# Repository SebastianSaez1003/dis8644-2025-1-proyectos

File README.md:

# dis8644-2025-1-proyectos

## acerca de

* Sigla: DIS8644
* Nombre: taller de diseño de máquinas eléctricas
* Escuela: Escuela de diseño
* Facultad: Facultad de Arquitectura, Arte y Diseño
* Universidad: Universidad Diego Portales.

dictado durante el primer semestre 2025 (marzo a julio)

## equipo docente

* aarón montoya <https://github.com/montoyamoraga/>
* matías serrano <https://github.com/misaaaaaa>
* andrés martin <https://github.com/AndresMartinM>

## enlaces a carpetas principales

* [00-proyecto-02](./00-proyecto-02/)
  * [00-proyecto-02/grupo-0a](./00-proyecto-02/grupo-0a/)
  * [00-proyecto-02/grupo-0b](./00-proyecto-02/grupo-0b/)
  * [00-proyecto-02/grupo-0c](./00-proyecto-02/grupo-0c/)
  * [00-proyecto-02/grupo-01](./00-proyecto-02/grupo-01/)
  * [00-proyecto-02/grupo-02](./00-proyecto-02/grupo-02/)
  * [00-proyecto-02/grupo-03](./00-proyecto-02/grupo-03/)
  * [00-proyecto-02/grupo-04](./00-proyecto-02/grupo-04/)
  * [00-proyecto-02/grupo-05](./00-proyecto-02/grupo-05/)
  * [00-proyecto-02/grupo-06](./00-proyecto-02/grupo-06/)
* [00-examen](./00-examen/)
  * [00-examen/grupo-0a](./00-examen/grupo-0a/)
  * [00-examen/grupo-0b](./00-examen/grupo-0b/)
  * [00-examen/grupo-0c](./00-examen/grupo-0c/)
  * [00-examen/grupo-01](./00-examen/grupo-01/)
  * [00-examen/grupo-02](./00-examen/grupo-02/)
  * [00-examen/grupo-03](./00-examen/grupo-03/)
  * [00-examen/grupo-04](./00-examen/grupo-04/)
  * [00-examen/grupo-05](./00-examen/grupo-05/)
  * [00-examen/grupo-06](./00-examen/grupo-06/)

## enlaces a carpetas de docentes

* [00-docentes](./00-docentes/)
* [00-info](./00-info/)

## enlaces a cada carpeta de estudiantes

* [01-sofiacartes](./01-sofiacartes/)
* [02-hazzaily](./02-hazzaily/)
* [03-antocristi](./03-antocristi/)
* [04-bumwox](./04-bumwox/)
* [05-brauliofigueroa2001](./05-brauliofigueroa2001/)
* [06-antfuentealba](./06-antfuentealba/)
* [07-clifford1one](./07-clifford1one/)
* [08-isabellagutierrezm](./08-isabellagutierrezm/)
* [98-Bernardita-lobo](./09-Bernardita-lobo/)
* [10-Anaisbmg](./10-Anaisbmg/)
* [11-zaaaiko](./11-zaaaiko/)
* [12-jotamorales-romulus](./12-jotamorales-romulus/)
* [13-Camila-Parada](./13-Camila-Parada/)
* [14-sofia-perezm](./14-sofia-perezm/)
* [15-sz-mada](./15-sz-mada/)
* [16-katalinariquelme](./16-katalinariquelme/)
* [17-felix-rg416](./17-felix-rg416/)
* [18-vxlentiinaa](./18-vxlentiinaa/)
* [19-SebastianSaez1003](./19-SebastianSaez1003/)
* [20-thyare08](./20-thyare08/)
* [21-duckusu](./21-duckusu/)
* [22-HSB25](./22-HSB25/)
* [23-FranUDP](./23-FranUDP/)
* [24-paulinavargasf](./24-paulinavargasf/)
* [25-AlanisMria](./25-AlanisMria/)
* [26-IzhakVillegas](./26-IzhakVillegas/)

## sesiones

nuestras sesiones de clases serán los martes y viernes entre marzo y julio 2025.

* 08:30am - 09:00am: preparación inicial, resolver dudas
* 09:00am - 10:30am: primera parte, foco contenidos y trabajo grupal de taller
* 10:30am - 11:00am: pausa
* 11:00am - 12:30pm: segunda parte, foco retroalimentación a estudiantes

## calendario detallado

| sesión                        | fecha    | temas                            |
| :---------------------------- | :--------| :--------------------------------|
| [13a](00-docentes/sesion-13a/)| 06-03 mar| feedback sobre proyecto-02       |
| [13b](00-docentes/sesion-13b/)| 06-06 vie| visita mbate - grupos proyecto-02|
| [14a](00-docentes/sesion-14a/)| 06-10 mar| prototipado proyecto-02: input   |
| [14b](00-docentes/sesion-14b/)| 06-13 vie| prototipado proyecto-02: output  |
| [15a](00-docentes/sesion-15a/)| 06-17 mar| prototipado proyecto-02          |
| [15b](00-docentes/sesion-15b/)| 06-20 vie| feriado, entrega noche anterior  |
| [16a](00-docentes/sesion-16a/)| 06-24 mar| salida:  palacio pereira         |
| [16b](00-docentes/sesion-16b/)| 06-27 vie| preparación examen - carcasas    |
| [00-examen](00-examen/)       | 07-11 vie| preparación examen - carcasas    |

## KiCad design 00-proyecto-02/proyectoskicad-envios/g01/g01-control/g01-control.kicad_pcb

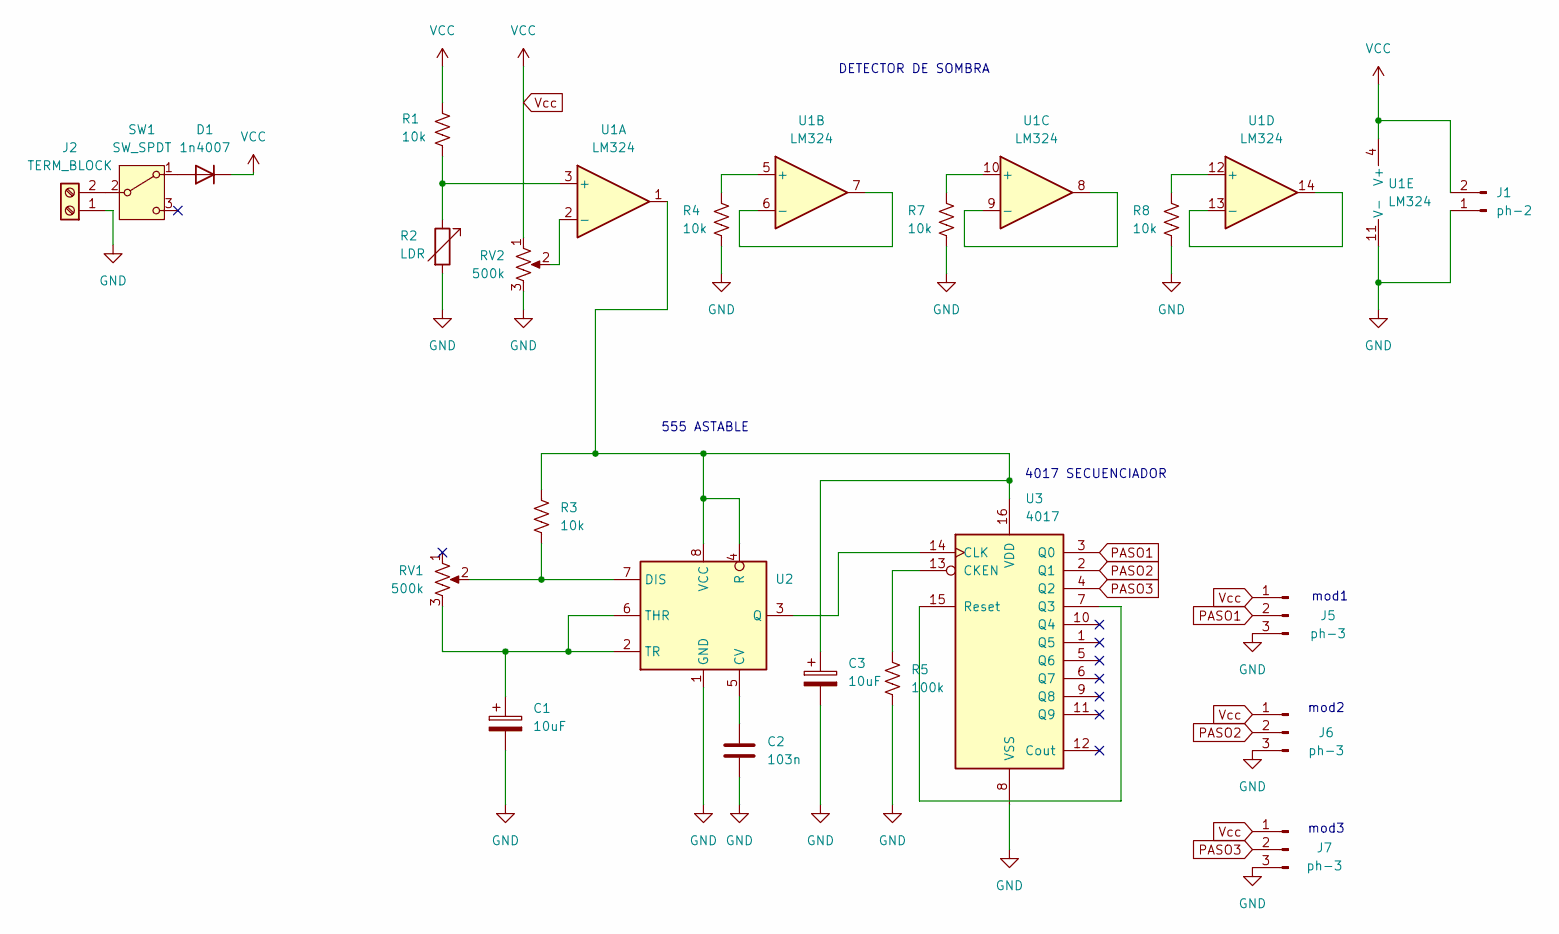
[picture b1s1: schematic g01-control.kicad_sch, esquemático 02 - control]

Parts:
C1, C3: 10uF; CP_Radial_D6.3mm_P2.50mm
C2: 103n; C_Disc_D6.0mm_W2.5mm_P5.00mm
D1: 1n4007; D_DO-41_SOD81_P10.16mm_Horizontal
J1: ph-2; PinHeader_1x02_P2.54mm_Vertical
J2: TERM_BLOCK; TerminalBlock_bornier-2_P5.08mm
J5, J6, J7: ph-3; PinHeader_1x03_P2.54mm_Vertical
R1, R3, R4, R7, R8: 10k; R_Axial_DIN0207_L6.3mm_D2.5mm_P10.16mm_Horizontal
R2: LDR; R_LDR_4.9x4.2mm_P2.54mm_Vertical
R5: 100k; R_Axial_DIN0207_L6.3mm_D2.5mm_P10.16mm_Horizontal
RV1, RV2: 500k; Potentiometer_Alps_RK163_Single_Horizontal
SW1: SW_SPDT; SW_Slide-03_Wuerth-WS-SLTV_10x2.5x6.4_P2.54mm
U1: LM324; DIP-14_W7.62mm_Socket_LongPads
U2: DIP-8_W7.62mm_Socket_LongPads
U3: 4017; DIP-16_W7.62mm_Socket_LongPads

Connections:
GND: C1.2, C2.2, C3.2, J1.1, J2.1, J5.3, J6.3, J7.3, R2.2, R4.2, R5.2, R7.2, R8.2, RV2.3, U1.11 (V-), U2.1 (GND), U3.8 (VSS); also elsewhere on the board
unnamed: D1.2 (A), SW1.1 (A)
unnamed: J2.2, SW1.2 (B)
unnamed: R1.2, R2.1, U1.3 (+)
unnamed: RV2.2, U1.2 (-)
unnamed: R4.1, U1.5 (+)
unnamed: U1.6 (-), U1.7
unnamed: R7.1, U1.10 (+)
unnamed: U1.8, U1.9 (-)
unnamed: R8.1, U1.12 (+)
unnamed: U1.13 (-), U1.14
unnamed: C2.1, U2.5 (CV)
unnamed: R3.2, RV1.2, U2.7 (DIS)
unnamed: U2.3 (Q), U3.14 (CLK)
unnamed: C3.1, R3.1, U1.1, U2.4 (R), U2.8 (VCC), U3.16 (VDD)
unnamed: C1.1, RV1.3, U2.2 (TR), U2.6 (THR)
unnamed: R5.1, U3.13 (CKEN)
unnamed: U3.7 (Q3), U3.15 (Reset)
PASO1: J5.2, U3.3 (Q0)
PASO2: J6.2, U3.2 (Q1)
PASO3: J7.2, U3.4 (Q2)
Vcc: D1.1 (K), J1.2, J5.1, J6.1, J7.1, R1.1, RV2.1, U1.4 (V+)

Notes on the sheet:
mod2
4017 SECUENCIADOR
555 ASTABLE
mod3
DETECTOR DE SOMBRA
mod1

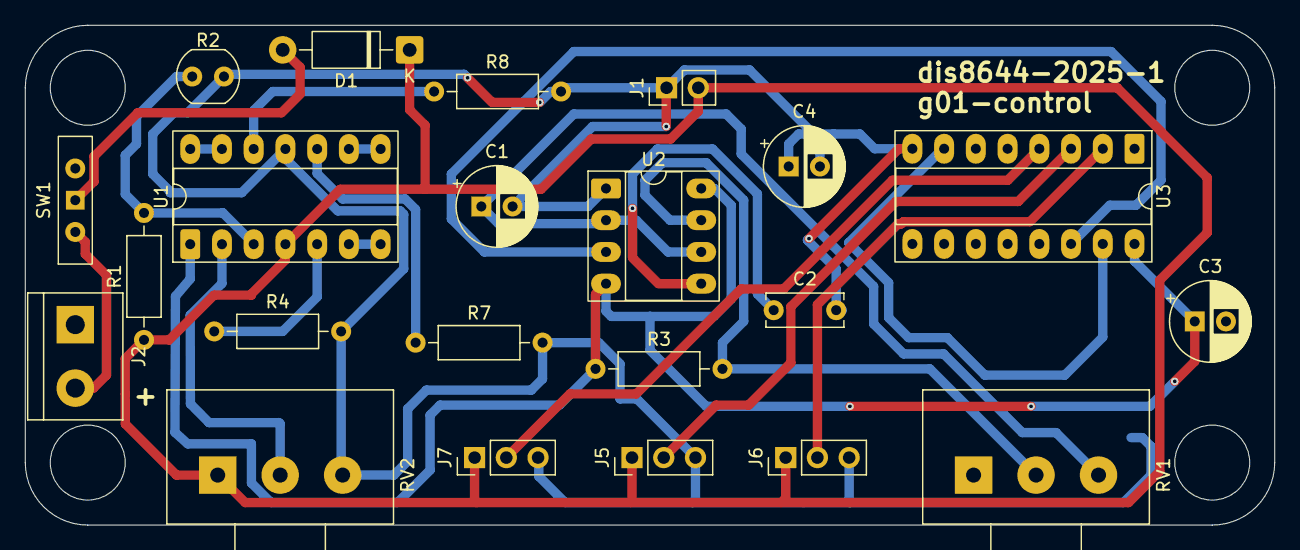
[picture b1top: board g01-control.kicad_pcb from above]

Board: 2 copper layers, 100.0 x 40.0 mm, 22 parts (0 on the bottom side), 21 nets.

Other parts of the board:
C4: 10uF; CP_Radial_D6.3mm_P2.50mm

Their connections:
GND: C4.1, C4.2; also elsewhere on the board

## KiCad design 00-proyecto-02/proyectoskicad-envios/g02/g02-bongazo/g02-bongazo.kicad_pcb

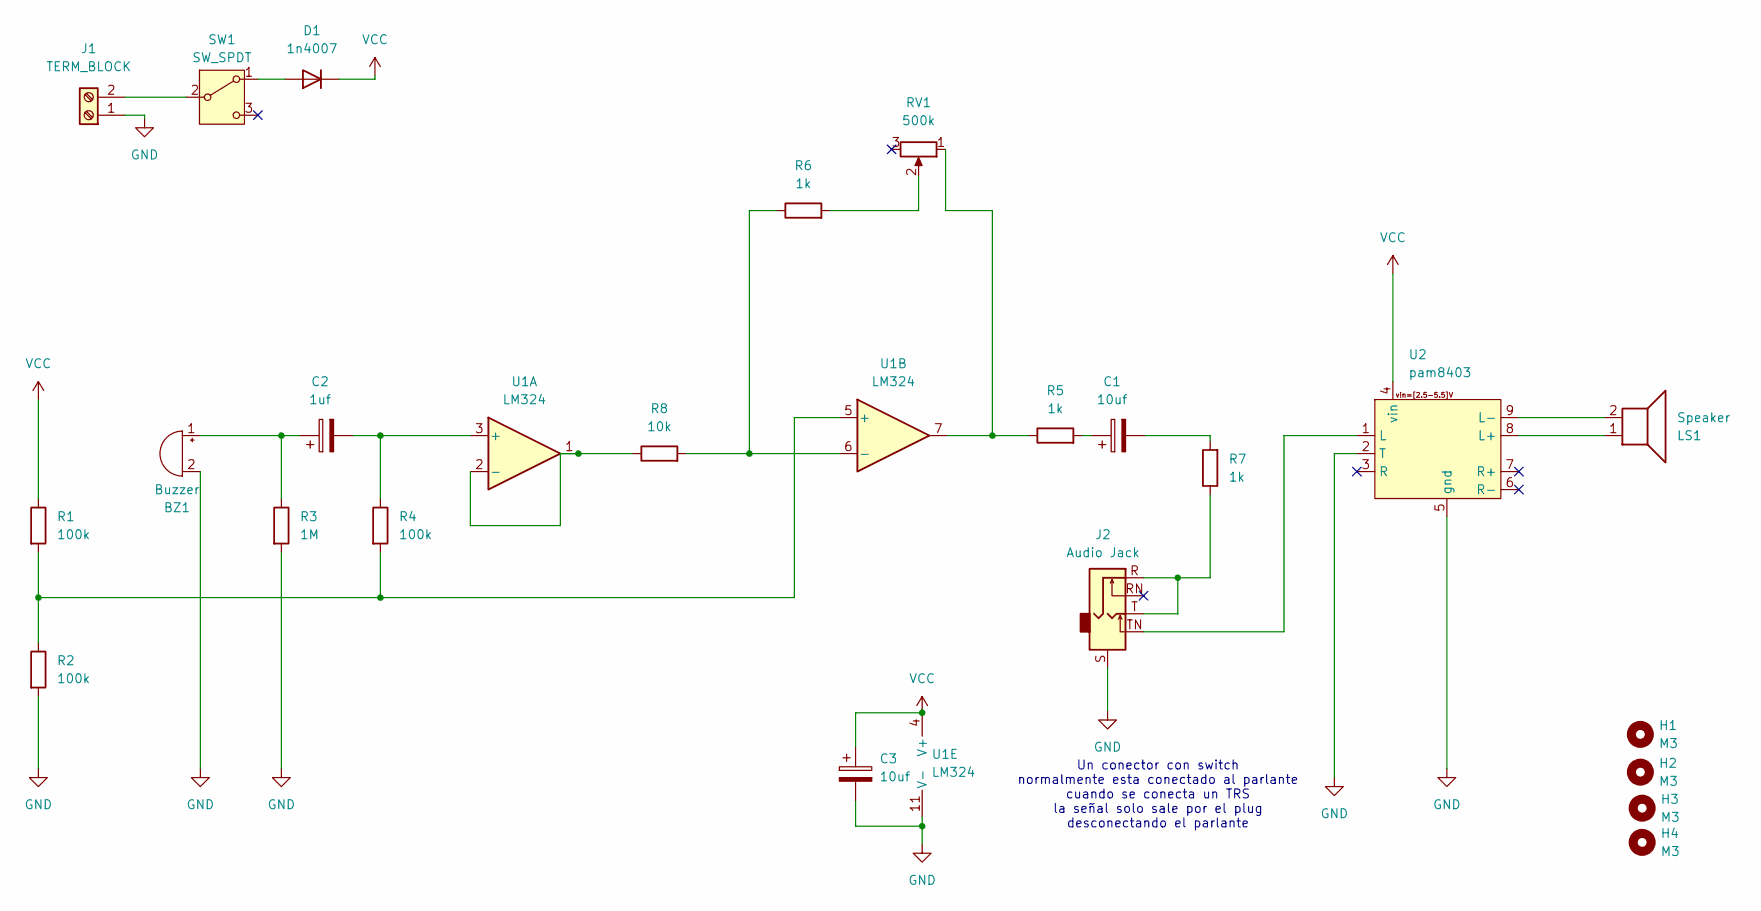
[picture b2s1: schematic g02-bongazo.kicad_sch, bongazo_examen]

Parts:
BZ1: Buzzer; Buzzer_12x9.5RM7.6
C1, C3: 10uf; CP_Radial_D6.3mm_P2.50mm
C2: 1uf; CP_Radial_D6.3mm_P2.50mm
D1: 1n4007; D_DO-41_SOD81_P12.70mm_Horizontal
H1, H2, H3, H4: M3; MountingHole_3.2mm_M3
J1: TERM_BLOCK; TerminalBlock_bornier-2_P5.08mm
J2: Audio Jack; Jack_6.35mm_Neutrik_NRJ6HM-1-AU_Horizontal
LS1: Speaker; TerminalBlock_MaiXu_MX126-5.0-02P_1x02_P5.00mm
R1, R2, R4: 100k; R_Axial_DIN0207_L6.3mm_D2.5mm_P10.16mm_Horizontal
R3: 1M; R_Axial_DIN0207_L6.3mm_D2.5mm_P10.16mm_Horizontal
R5, R6, R7: 1k; R_Axial_DIN0207_L6.3mm_D2.5mm_P10.16mm_Horizontal
R8: 10k; R_Axial_DIN0207_L6.3mm_D2.5mm_P10.16mm_Horizontal
RV1: 500k; Potentiometer_Alps_RK163_Single_Horizontal
SW1: SW_SPDT; SW_Slide-03_Wuerth-WS-SLTV_10x2.5x6.4_P2.54mm
U1: LM324; DIP-14_W7.62mm
U2: pam8403

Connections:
GND: BZ1.2 (-), C3.2, J1.1, J2.S, R2.2, R3.2, U1.11 (V-), U2.2 (T), U2.5 (gnd)
unnamed: BZ1.1 (+), C2.1, R3.1
unnamed: C1.1, R5.2
unnamed: C1.2, R7.2
unnamed: D1.2 (A), SW1.1 (A)
unnamed: J1.2, SW1.2 (B)
unnamed: J2.R, J2.T, R7.1
unnamed: R5.1, RV1.1, U1.7
unnamed: R6.2, RV1.2
unnamed: C2.2, R4.1, U1.3 (+)
unnamed: R8.1, U1.1, U1.2 (-)
unnamed: R1.2, R2.1, R4.2, U1.5 (+)
unnamed: R6.1, R8.2, U1.6 (-)
unnamed: J2.TN, U2.1 (L)
unnamed: LS1.1, U2.8 (L+)
unnamed: LS1.2, U2.9 (L-)
VCC: C3.1, D1.1 (K), R1.1, U1.4 (V+), U2.4 (vin)

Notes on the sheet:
Un conector con switch normalmente esta conectado al parlante cuando se conecta un TRS la señal solo sale por el plug desconectando el parlante

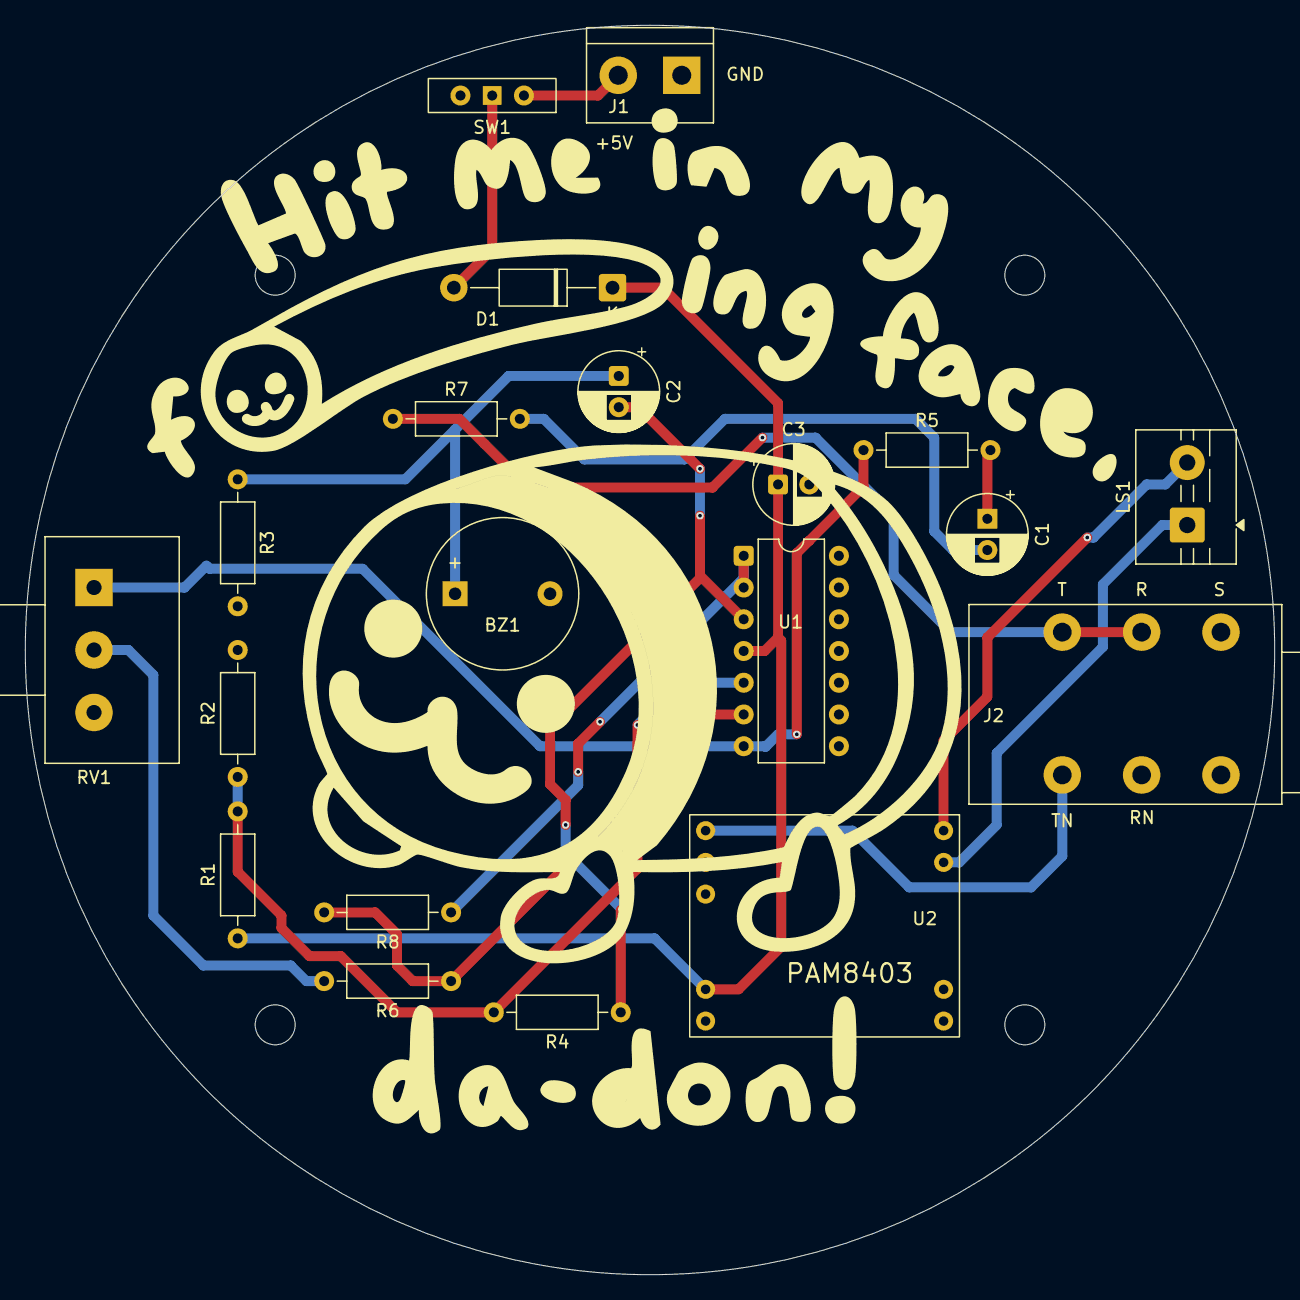
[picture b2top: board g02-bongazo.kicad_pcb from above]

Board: 2 copper layers, 100.0 x 100.0 mm, 24 parts (0 on the bottom side), 17 nets.

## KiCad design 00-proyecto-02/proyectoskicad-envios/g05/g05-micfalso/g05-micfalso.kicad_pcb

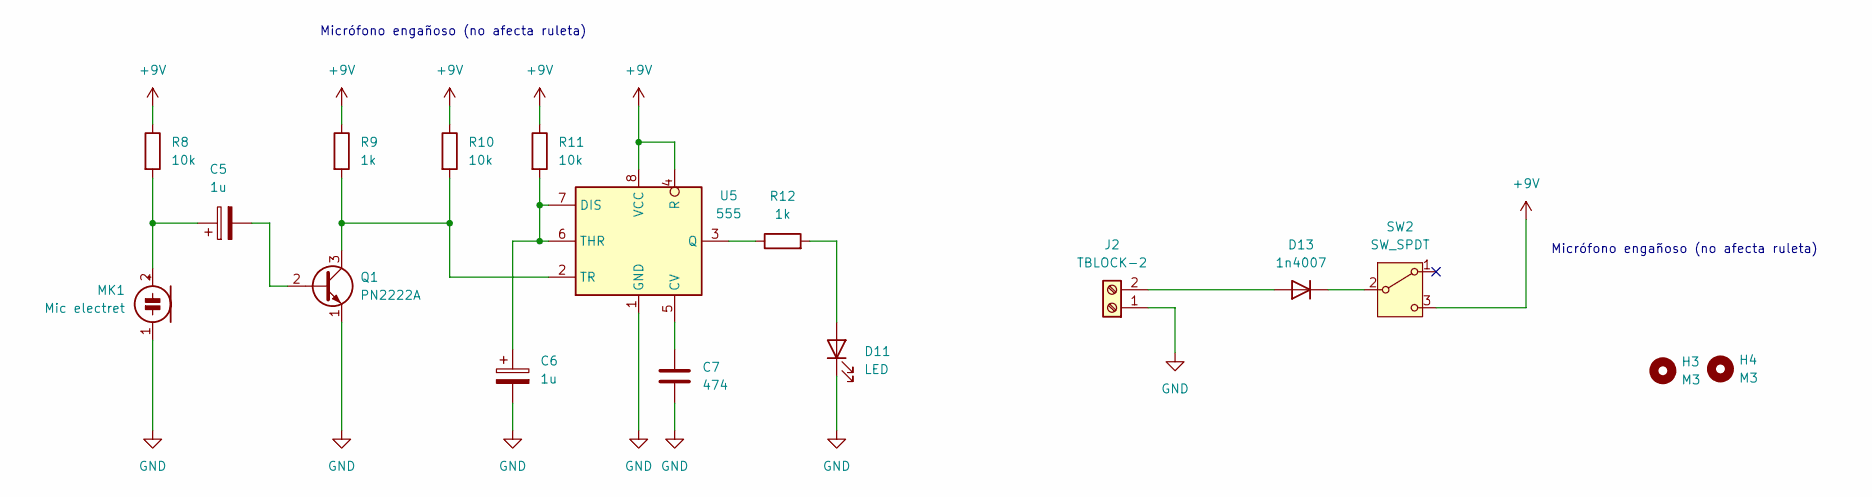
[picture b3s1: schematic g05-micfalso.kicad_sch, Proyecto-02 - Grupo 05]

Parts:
C5, C6: 1u; CP_Radial_D6.3mm_P2.50mm
C7: 474; C_Disc_D5.0mm_W2.5mm_P5.00mm
D11: LED; LED_D5.0mm
D13: 1n4007; D_DO-41_SOD81_P10.16mm_Horizontal
H3, H4: M3; MountingHole_3.2mm_M3
J2: TBLOCK-2; TerminalBlock_MaiXu_MX126-5.0-02P_1x02_P5.00mm
MK1: Mic electret; POM-2244P-C3310-2-R
Q1: PN2222A; TO-92_Inline_Wide
R8, R10, R11: 10k; R_Axial_DIN0207_L6.3mm_D2.5mm_P10.16mm_Horizontal
R9, R12: 1k; R_Axial_DIN0207_L6.3mm_D2.5mm_P10.16mm_Horizontal
SW2: SW_SPDT; SPDT_PCB_small_P2.5mm
U5: 555; DIP-8_W7.62mm_Socket_LongPads

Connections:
+9V: R8.1, R9.1, R10.1, R11.1, SW2.3 (C), U5.4 (R), U5.8 (VCC)
GND: C6.2, C7.2, D11.1 (K), J2.1, MK1.1 (-), Q1.1 (E), U5.1 (GND)
unnamed: D11.2 (A), R12.2
unnamed: D13.2 (A), J2.2
unnamed: D13.1 (K), SW2.2 (B)
unnamed: C5.1, MK1.2 (+), R8.2
unnamed: C5.2, Q1.2 (B)
unnamed: Q1.3 (C), R9.2, R10.2, U5.2 (TR)
unnamed: C7.1, U5.5 (CV)
unnamed: C6.1, R11.2, U5.6 (THR), U5.7 (DIS)
unnamed: R12.1, U5.3 (Q)

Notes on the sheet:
Micrófono engañoso (no afecta ruleta)

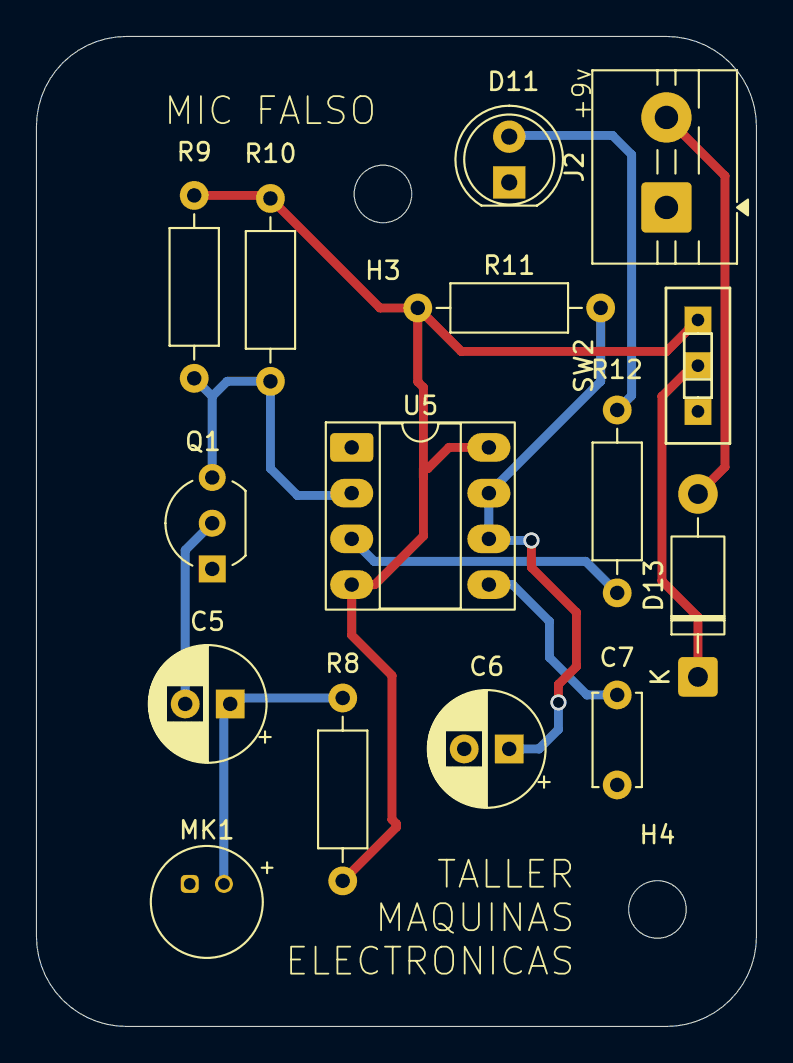
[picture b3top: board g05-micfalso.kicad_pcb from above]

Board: 2 copper layers, 40.0 x 55.0 mm, 17 parts (0 on the bottom side), 11 nets.

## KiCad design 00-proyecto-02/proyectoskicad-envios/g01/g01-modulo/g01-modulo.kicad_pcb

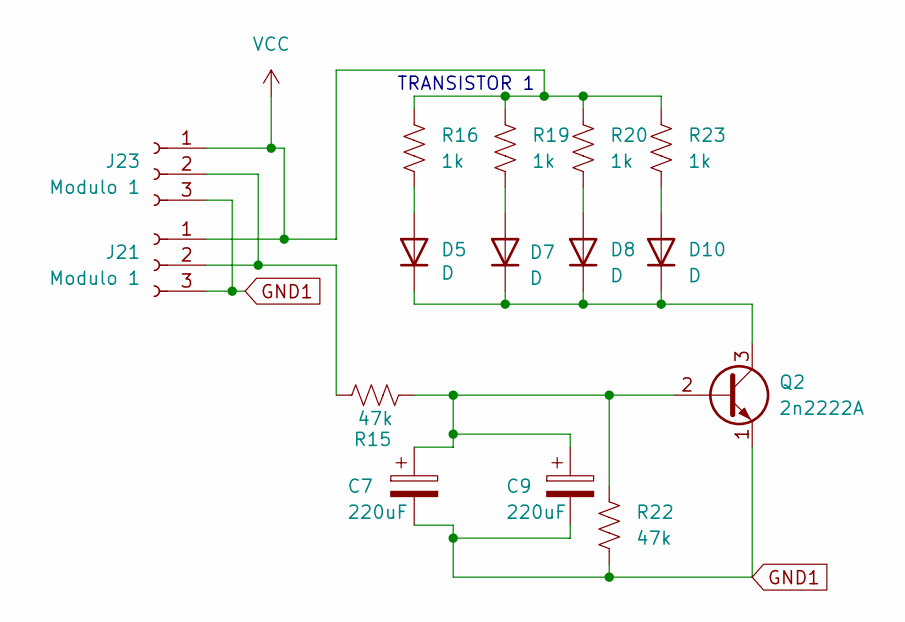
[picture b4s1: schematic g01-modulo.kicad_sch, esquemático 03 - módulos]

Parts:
C7, C9: 220uF; CP_Radial_D6.3mm_P2.50mm
D5, D7, D8, D10: D; LED_D5.0mm
J21, J23: Modulo 1; PinHeader_1x03_P2.54mm_Vertical
Q2: 2n2222A; TO-92
R15, R22: 47k; R_Axial_DIN0207_L6.3mm_D2.5mm_P10.16mm_Horizontal
R16, R19, R20, R23: 1k; R_Axial_DIN0207_L6.3mm_D2.5mm_P10.16mm_Horizontal

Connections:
GND1: C7.2, C9.2, J21.3, J23.3, Q2.1 (E), R22.2
unnamed: D5.2 (A), R16.2
unnamed: D7.2 (A), R19.2
unnamed: D8.2 (A), R20.2
unnamed: D10.2 (A), R23.2
unnamed: D5.1 (K), D7.1 (K), D8.1 (K), D10.1 (K), Q2.3 (C)
unnamed: J21.2, J23.2, R15.1
unnamed: C7.1, C9.1, Q2.2 (B), R15.2, R22.1
VCC: J21.1, J23.1, R16.1, R19.1, R20.1, R23.1

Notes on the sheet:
TRANSISTOR 1

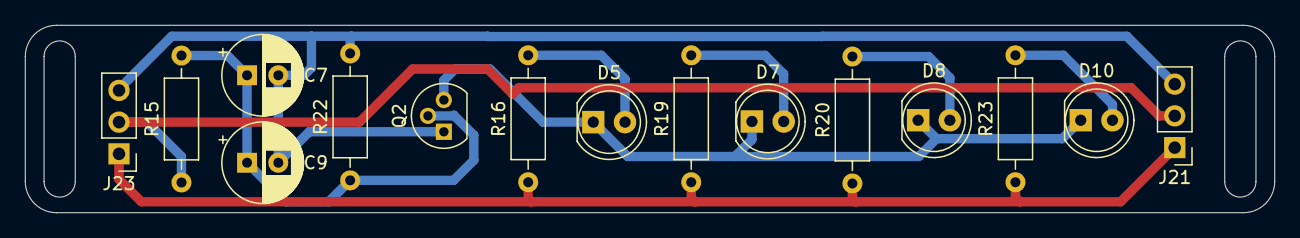
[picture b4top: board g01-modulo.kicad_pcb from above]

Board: 2 copper layers, 100.0 x 15.0 mm, 15 parts (0 on the bottom side), 9 nets.

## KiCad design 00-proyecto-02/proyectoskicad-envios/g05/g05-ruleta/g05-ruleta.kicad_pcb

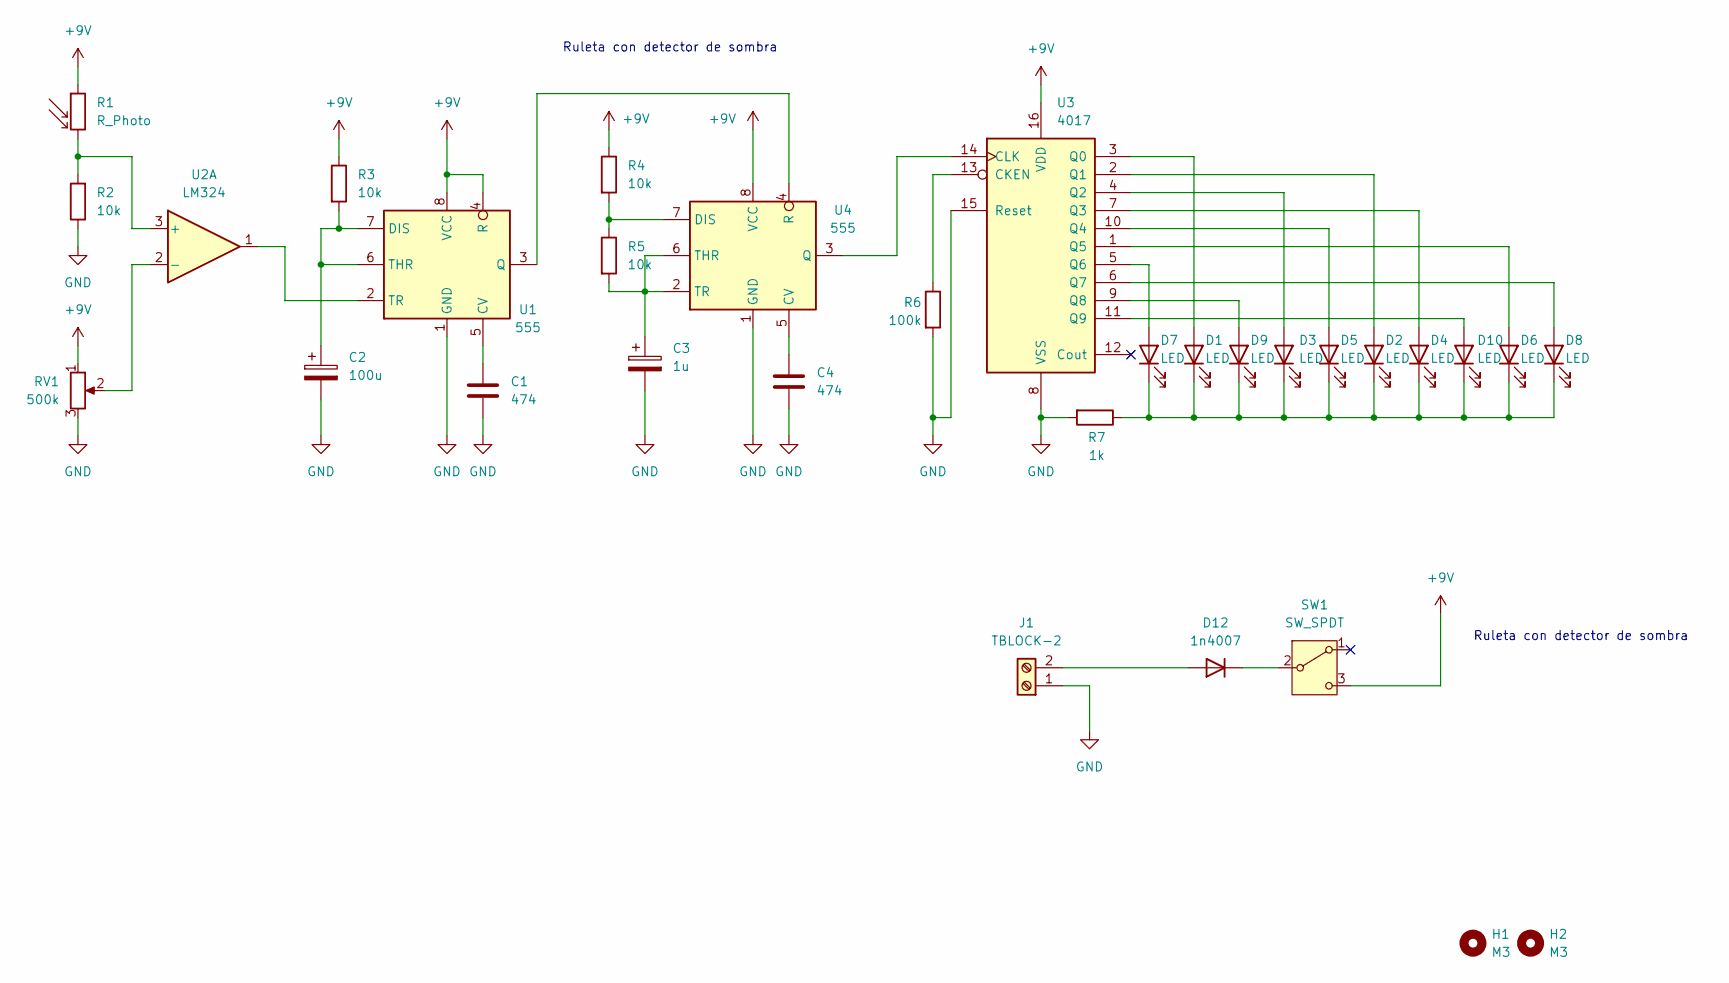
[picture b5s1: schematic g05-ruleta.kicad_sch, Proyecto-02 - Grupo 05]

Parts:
C1, C4: 474; C_Disc_D5.0mm_W2.5mm_P5.00mm
C2: 100u; CP_Radial_D6.3mm_P2.50mm
C3: 1u; CP_Radial_D6.3mm_P2.50mm
D1, D2, D3, D4, D5, D6, D7, D8, D9, D10: LED; LED_D5.0mm
D12: 1n4007; D_DO-41_SOD81_P10.16mm_Horizontal
H1, H2: M3; MountingHole_3.2mm_M3
J1: TBLOCK-2; TerminalBlock_MaiXu_MX126-5.0-02P_1x02_P5.00mm
R1: R_Photo; R_LDR_5.1x4.3mm_P3.4mm_Vertical
R2, R3, R4, R5: 10k; R_Axial_DIN0207_L6.3mm_D2.5mm_P10.16mm_Horizontal
R6: 100k; R_Axial_DIN0207_L6.3mm_D2.5mm_P10.16mm_Horizontal
R7: 1k; R_Axial_DIN0207_L6.3mm_D2.5mm_P10.16mm_Horizontal
RV1: 500k; Potentiometer_Piher_T-16H_Single_Horizontal
SW1: SW_SPDT; SPDT_PCB_small_P2.5mm
U1, U4: 555; DIP-8_W7.62mm_Socket_LongPads
U2: LM324; DIP-14_W7.62mm_Socket_LongPads
U3: 4017; DIP-16_W7.62mm_Socket_LongPads

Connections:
+9V: R1.1, R3.1, R4.1, RV1.1, SW1.3 (C), U1.4 (R), U1.8 (VCC), U3.16 (VDD), U4.8 (VCC)
GND: C1.2, C2.2, C3.2, C4.2, J1.1, R2.1, R6.2, R7.2, RV1.3, U1.1 (GND), U3.8 (VSS), U3.15 (Reset), U4.1 (GND)
unnamed: D1.2 (A), U3.3 (Q0)
unnamed: D1.1 (K), D2.1 (K), D3.1 (K), D4.1 (K), D5.1 (K), D6.1 (K), D7.1 (K), D8.1 (K), D9.1 (K), D10.1 (K), R7.1
unnamed: D2.2 (A), U3.2 (Q1)
unnamed: D3.2 (A), U3.4 (Q2)
unnamed: D4.2 (A), U3.7 (Q3)
unnamed: D5.2 (A), U3.10 (Q4)
unnamed: D6.2 (A), U3.1 (Q5)
unnamed: D7.2 (A), U3.5 (Q6)
unnamed: D8.2 (A), U3.6 (Q7)
unnamed: D9.2 (A), U3.9 (Q8)
unnamed: D10.2 (A), U3.11 (Q9)
unnamed: D12.2 (A), J1.2
unnamed: D12.1 (K), SW1.2 (B)
unnamed: C1.1, U1.5 (CV)
unnamed: C2.1, R3.2, U1.6 (THR), U1.7 (DIS)
unnamed: U1.3 (Q), U4.4 (R)
unnamed: U1.2 (TR), U2.1
unnamed: R1.2, R2.2, U2.3 (+)
unnamed: RV1.2, U2.2 (-)
unnamed: R6.1, U3.13 (CKEN)
unnamed: U3.14 (CLK), U4.3 (Q)
unnamed: C4.1, U4.5 (CV)
unnamed: R4.2, R5.1, U4.7 (DIS)
unnamed: C3.1, R5.2, U4.2 (TR), U4.6 (THR)

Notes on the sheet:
Ruleta con detector de sombra

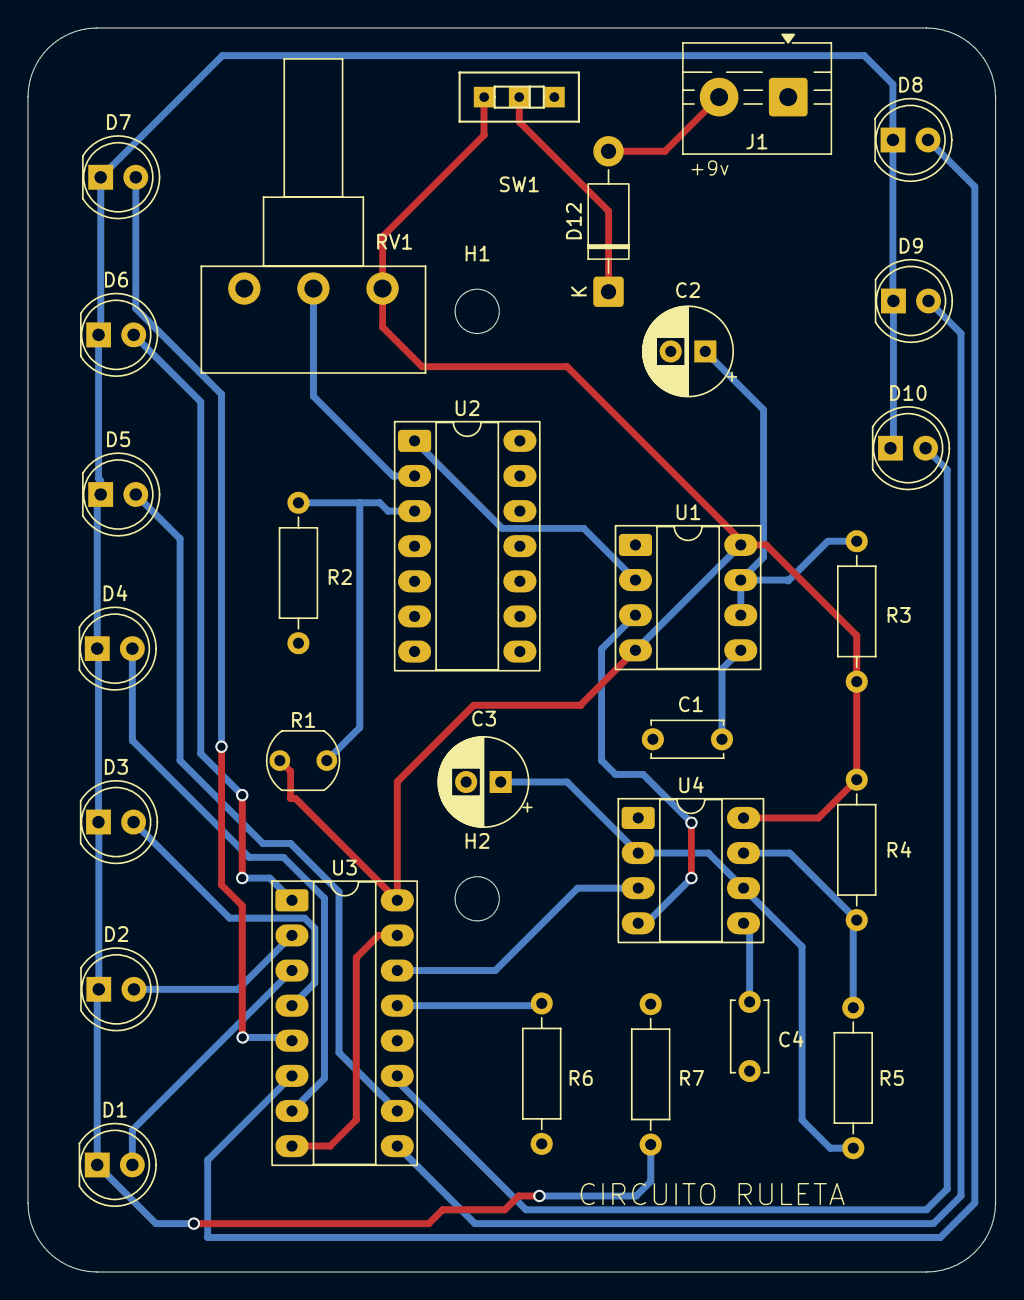
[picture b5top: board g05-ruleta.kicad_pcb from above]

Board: 2 copper layers, 70.0 x 90.0 mm, 31 parts (0 on the bottom side), 26 nets.

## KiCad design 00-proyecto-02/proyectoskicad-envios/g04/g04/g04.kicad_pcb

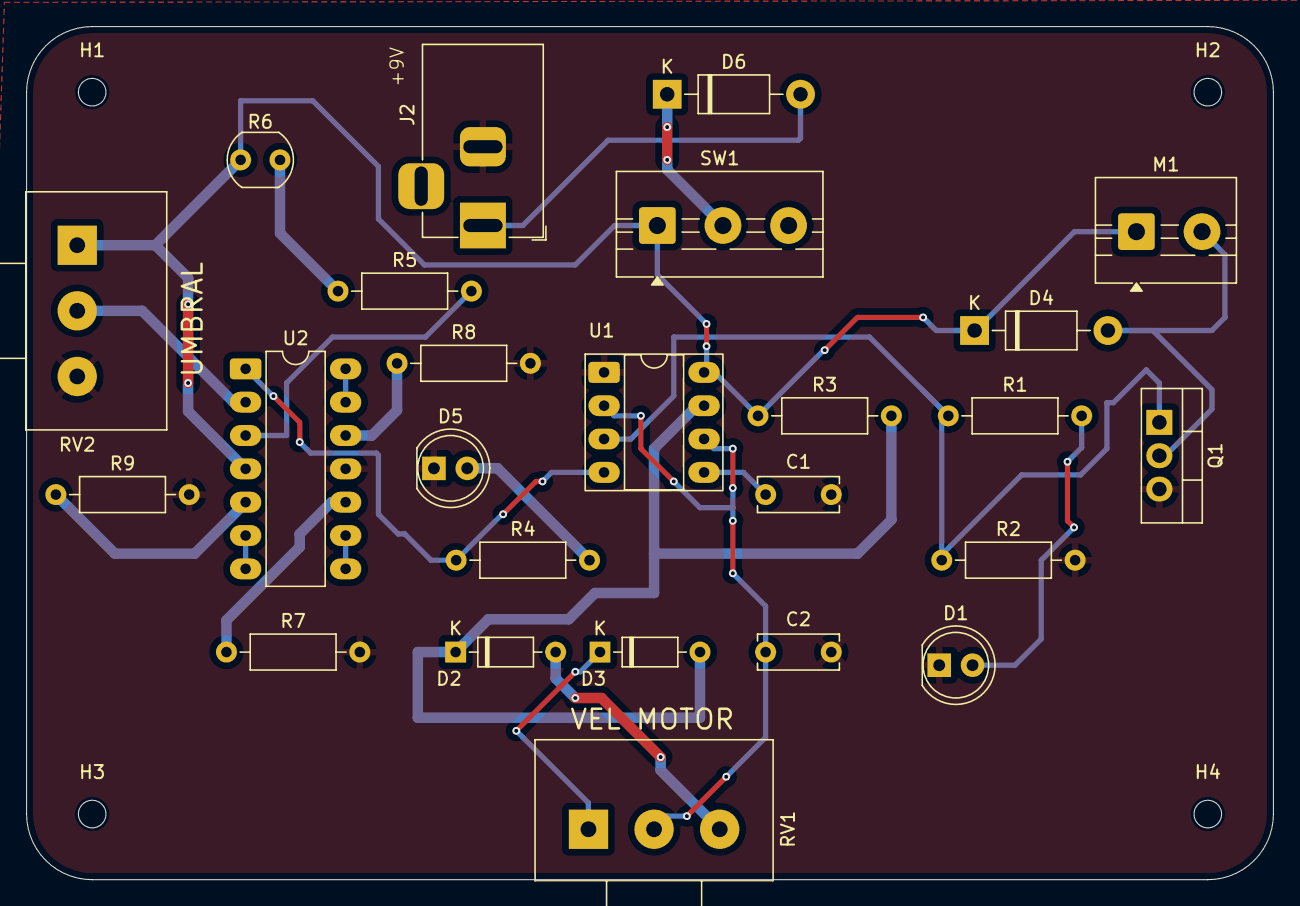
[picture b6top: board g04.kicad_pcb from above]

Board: 2 copper layers, 95.0 x 65.0 mm, 29 parts (0 on the bottom side), 23 nets.

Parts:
C1, C2: 104; C_Disc_D6.0mm_W2.5mm_P5.00mm
D1, D5: LED; LED_D5.0mm
D2, D3: 1N4148; D_DO-35_SOD27_P7.62mm_Horizontal
D4, D6: 1N4007; D_DO-41_SOD81_P10.16mm_Horizontal
H1, H2, H3, H4: MountingHole; MountingHole_2.1mm
J2: Barrel_Jack_Switch; BarrelJack_Horizontal
M1: Motor_DC; TerminalBlock_MaiXu_MX126-5.0-02P_1x02_P5.00mm
Q1: IRLZ44N; TO-220-3_Vertical
R1, R3, R4: 1k; R_Axial_DIN0207_L6.3mm_D2.5mm_P10.16mm_Horizontal
R2: 100k; R_Axial_DIN0207_L6.3mm_D2.5mm_P10.16mm_Horizontal
R5, R7, R8, R9: 10k; R_Axial_DIN0207_L6.3mm_D2.5mm_P10.16mm_Horizontal
R6: LDR; R_LDR_5.0x4.1mm_P3mm_Vertical
RV1, RV2: 500k; Potentiometer_Alps_RK163_Single_Horizontal
SW1: SW_SPDT; TerminalBlock_MaiXu_MX126-5.0-03P_1x03_P5.00mm
U1: DIP-8_W7.62mm_Socket_LongPads
U2: LM324; DIP-14_W7.62mm_LongPads

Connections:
GND: C1.2, C2.2, D1.1 (K), D5.1 (K), J2.2, Q1.3 (S), R2.2, R7.2, R8.2, R9.2, RV2.3, U1.1 (GND), U2.11 (V-)
unnamed: D1.2 (A), R1.2
unnamed: D2.2 (A), RV1.3
unnamed: D2.1 (K), D3.2 (A), R3.2, U1.7 (DIS)
unnamed: D3.1 (K), RV1.1
unnamed: D4.2 (A), M1.2 (-), Q1.2 (D)
unnamed: D5.2 (A), R4.2
unnamed: D6.2 (A), J2.1
unnamed: D6.1 (K), SW1.2 (B)
unnamed: Q1.1 (G), R1.1, R2.1, U1.3 (Q)
unnamed: R5.1, R6.2
unnamed: C1.1, U1.5 (CV)
unnamed: R4.1, U1.4 (R), U2.1
unnamed: C2.1, RV1.2, U1.2 (TR), U1.6 (THR)
unnamed: R5.2, U2.3 (+)
unnamed: RV2.2, U2.2 (-)
unnamed: R9.1, U2.5 (+)
unnamed: U2.6 (-), U2.7
unnamed: R7.1, U2.10 (+)
unnamed: U2.8, U2.9 (-)
unnamed: R8.1, U2.12 (+)
unnamed: U2.13 (-), U2.14
VCC: D4.1 (K), M1.1 (+), R3.1, R6.1, RV2.1, SW1.1 (A), U1.8 (VCC), U2.4 (V+)

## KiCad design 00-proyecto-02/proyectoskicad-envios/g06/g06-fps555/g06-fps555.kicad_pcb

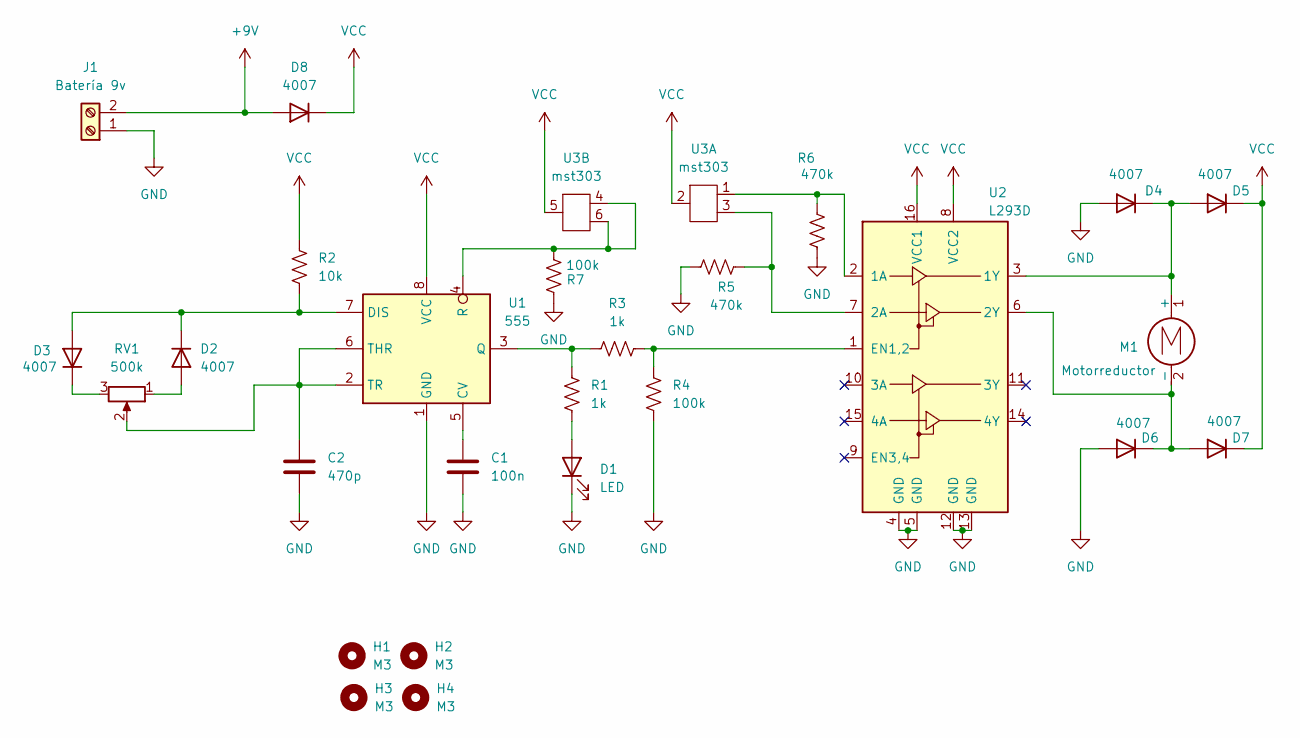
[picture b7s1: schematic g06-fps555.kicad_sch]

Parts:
C1: 100n; C_Disc_D5.0mm_W2.5mm_P2.50mm
C2: 470p; C_Disc_D5.1mm_W3.2mm_P5.00mm
D1: LED; LED_D3.0mm_Clear
D2, D3, D4, D5, D6, D7, D8: 4007; D_A-405_P10.16mm_Horizontal
H1, H2, H3, H4: M3; MountingHole_3.2mm_M3
J1: Batería 9v; TerminalBlock_MaiXu_MX126-5.0-02P_1x02_P5.00mm
M1: Motorreductor; TerminalBlock_MaiXu_MX126-5.0-02P_1x02_P5.00mm
R1, R3: 1k; R_Axial_DIN0207_L6.3mm_D2.5mm_P10.16mm_Horizontal
R2: 10k; R_Axial_DIN0207_L6.3mm_D2.5mm_P10.16mm_Horizontal
R4, R7: 100k; R_Axial_DIN0207_L6.3mm_D2.5mm_P10.16mm_Horizontal
R5, R6: 470k; R_Axial_DIN0207_L6.3mm_D2.5mm_P10.16mm_Horizontal
RV1: 500k; Potentiometer_Omeg_PC16BU_Vertical
U1: 555; DIP-8_W7.62mm_Socket_LongPads
U2: L293D; DIP-16_W7.62mm
U3: mst303; PinHeader_2x03_P2.54mm_Vertical

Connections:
+9V: D8.2 (A), J1.2
GND: C1.2, C2.2, D1.1 (K), D4.2 (A), D6.2 (A), J1.1, R4.2, R5.1, R6.1, R7.1, U1.1 (GND), U2.4 (GND), U2.5 (GND), U2.12 (GND), U2.13 (GND)
unnamed: D1.2 (A), R1.2
unnamed: D2.2 (A), RV1.1
unnamed: D2.1 (K), D3.2 (A), R2.2, U1.7 (DIS)
unnamed: D3.1 (K), RV1.3
unnamed: D4.1 (K), D5.2 (A), M1.1 (+), U2.3 (1Y)
unnamed: D6.1 (K), D7.2 (A), M1.2 (-), U2.6 (2Y)
unnamed: C1.1, U1.5 (CV)
unnamed: R1.1, R3.1, U1.3 (Q)
unnamed: R7.2, U1.4 (R), U3.4, U3.6
unnamed: C2.1, RV1.2, U1.2 (TR), U1.6 (THR)
unnamed: R6.2, U2.2 (1A), U3.1
unnamed: R5.2, U2.7 (2A), U3.3
unnamed: R3.2, R4.1, U2.1 (EN1,2)
VCC: D5.1 (K), D7.1 (K), D8.1 (K), R2.1, U1.8 (VCC), U2.8 (VCC2), U2.16 (VCC1), U3.2, U3.5

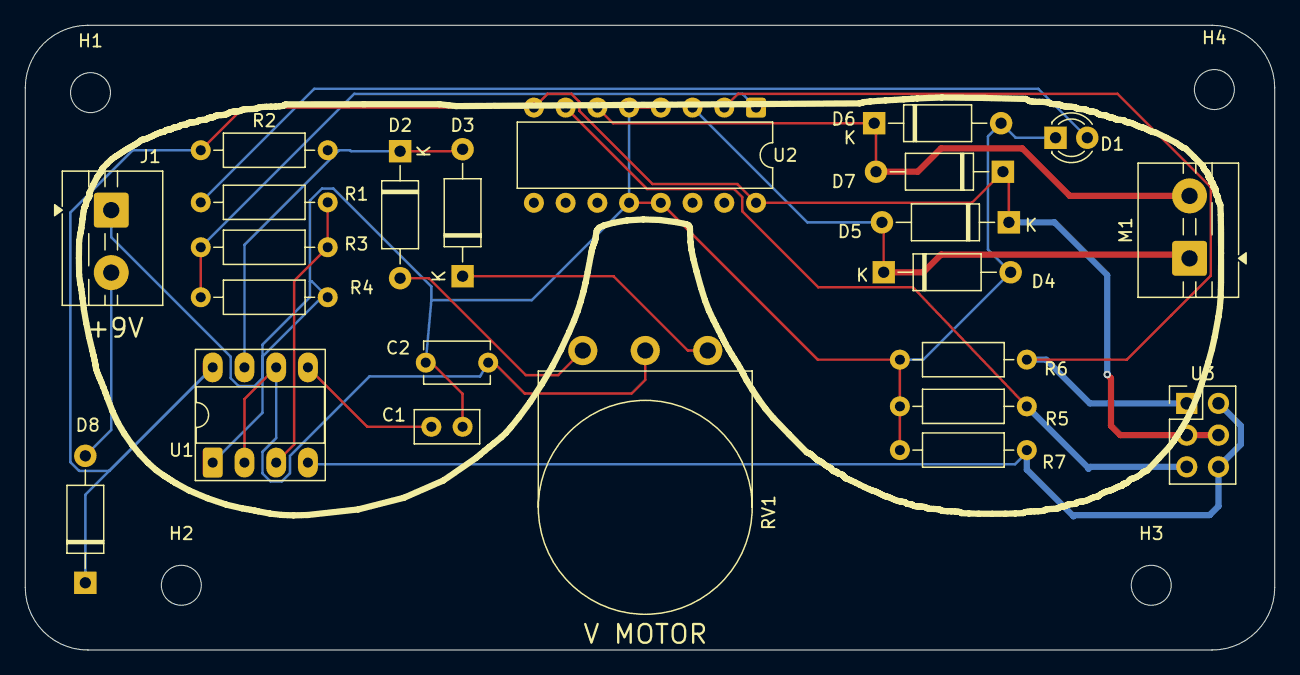
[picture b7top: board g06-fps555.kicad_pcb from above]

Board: 2 copper layers, 100.0 x 50.0 mm, 27 parts (0 on the bottom side), 16 nets.
